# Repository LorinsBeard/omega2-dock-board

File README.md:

# Omega2 Dock board

Inspired by [Omega dock\new](https://github.com/5N44P/omega-dock-new) board.

## Overview

This is yet another dock for Onion Omega2/Omega2+ single board computers. 
Main board features:

* Ethernet socket
* USB type A Host
* Micro USB power and UART
* Expansion pins
* User Button and LED

## BOM

BOM is also available in CSV format.

| Reference | Quantity | Description | MPN | Manufacturer | Datasheet |
|-----------|---------:|-------------|-----|--------------|-----------|
| C10 C2  | 2 | CAP CER 10UF 6.3V X5R 0603 | CL10A106MQ8NNNC | Samsung Electro-Mechanics | [link](http://www.samsungsem.com/kr/support/product-search/mlcc/__icsFiles/afieldfile/2018/06/20/CL10A106MQ8NNNC.pdf) |
| C4 C5  | 2 | CAP CER 22pF 50V NPO 0603 | CL10C220JB8NNN | Samsung Electro-Mechanics | [link](www.samsungsem.com/global/front/downloadcms.do?path=%2F%2Fglobal%2F%2Fsupport%2F%2Fproduct-search%2F%2Fmlcc%2F%2F__icsFiles%2F%2Fafieldfile%2F%2F2016%2F%2F08%2F%2F18&fileName=S_CL10C220JB8NNNL.pdf) |
| C6 C8 C7 C1 C3  | 5 | CAP CER 0.1UF 50V X7R 0603 | CL10B104KB8NNNC | Samsung Electro-Mechanics | [link](http://www.samsungsem.com/kr/support/product-search/mlcc/__icsFiles/afieldfile/2018/07/24/CL10B104KB8NNNC.pdf) |
| C9  | 1 | CAP CER 1UF 16V X7R 0603 | CL10B105KO8NNNC | Samsung Electro-Mechanics | [link](http://www.samsungsem.com/kr/support/product-search/mlcc/__icsFiles/afieldfile/2019/06/18/CL10B105KO8NNNC-19.pdf) |
| D2 D1  | 2 | TVS DIODE 5.25V 17V SOT23-6 | USBLC6-2SC6 | STMicroelectronics | [link](http://www.st.com/content/ccc/resource/technical/document/datasheet/06/1d/48/9c/6c/20/4a/b2/CD00050750.pdf/files/CD00050750.pdf/jcr:content/translations/en.CD00050750.pdf) |
| D3 D4  | 2 | LED Yellow Green 0603 30mA | FYLS-0603GD | FORYARD OPTOELECTRONICS | [link](http://www.foryard-led.ru/pdf/fyls-0603gd.pdf) |
| F1  | 1 | PTC RESET FUSE 6V 1.1A 1206 | MF-NSMF110-2 | Bourns | [link](https://www.bourns.com/docs/Product-Datasheets/mfnsmf.pdf) |
| J1  | 1 | CONN RCPT USB2.0 MICRO B SMD R/A | 10118194-0001LF | Amphenol ICC (FCI) | [link](http://www.amphenol-icc.com/media/wysiwyg/files/drawing/10118194.pdf) |
| J2  | 1 | CONN RCPT USB2.0 TYPEA 4POS R/A | KLS1-181A-W | KLS | [link](http://www.klsele.com/admin/product_upload/20190917081512KLS1-1811%20A%20Female%20Dip%2090%20USB%20Connector%202.jpg.pdf) |
| J3  | 1 | CONN F HEADER 26POS 2.54mm | ZL262-26DG | CONNFLY | [link](http://www.kosmodrom.com.ua/pdf/zl262-dg.pdf) |
| J4  | 1 | CONN M HEADER 6 POS 2.54mm | ZL201-06G | CONNFLY | [link](http://www.kosmodrom.com.ua/pdf/zl201.pdf) |
| J5  | 1 | RJ45 connector with transformer | KLS12-TL002R-1*1-G/Y-1-03 | KLS | [link](http://www.klsele.com/admin/product_upload/20170620132005KLS12-TL002-1X1.pdf) |
| R1 R3  | 2 | SMD RES 0603 10 kOhm 100mW 50V | RC0603FR-10KR | Hitano | [link](https://www.rcscomponents.kiev.ua/datasheets/komechip-eesistor-datasheet.pdf) |
| R11 R7 R6 R10  | 4 | SMD RES 0603 49.9 Ohm 100mW 50V | RC0603FR-49R9 | Hitano | [link](https://www.rcscomponents.kiev.ua/datasheets/rc_series_hitano-datasheet.pdf) |
| R12 R4 R5 R8 R9 R2 R13  | 7 | SMD RES 0603 470 Ohm 100mW 50V | RC0603JR-470R | Hitano | [link](https://www.rcscomponents.kiev.ua/datasheets/rc_series_hitano-datasheet.pdf) |
| SW2 SW1  | 2 | SWITCH TACTILE SPST-NO 0.05A 12V | TACTM-24N-F | NINIGI | [link](https://en.ninigi.com/product/tactm-24n-f/pdf) |
| U1  | 1 | USB UART CONVERTER 16SOIC | CH340G | WCH | [link](www.datasheet5.com/pdf-local-2195953) |
| U2  | 1 | SBC  | Omega2 | Onion | [link](https://docs.onion.io/omega2-docs/omega2p.html) |
| U3  | 1 | IC REG LINEAR 3.3V 800MA SOT223  | LD1117S33TR | STMicroelectronics | [link](https://www.st.com/content/ccc/resource/technical/document/datasheet/99/3b/7d/91/91/51/4b/be/CD00000544.pdf/files/CD00000544.pdf/jcr:content/translations/en.CD00000544.pdf) |
| Y1  | 1 | Quartz Crystal SMD 12.0 MHz | 12.88662 | GEYER | [link](https://www.geyer-electronic.com/fileadmin/user_upload/frequenz/quartz/KX-7/GEYER-KX-7.pdf) |

Note:

I have bought a KLS Ethernet connector for **J5** but used a footprint for [Amphenol ICC RJMG1BD3B8K1ANR](https://www.digikey.com/product-detail/en/amphenol-icc-commercial-products/RJMG1BD3B8K1ANR/RJMG1BD3B8K1ANR-ND/5359794) connector. There is just one difference - **reversed pinout** for Yellow LED. 

Also, I have bought a KLS USB A connector for **J2** and used an [Amphenol ICC UE27AC54100](https://www.digikey.com/product-detail/en/amphenol-icc-commercial-products/UE27AC54100/UE27AC54100-ND) footprint, but they are similar, though.

## Schematic & PCB

Designed using **KiCAD**. Also, I have take some parts from [Digi-Key Kicad library](https://www.digikey.com/en/resources/design-tools/kicad). 

The library with footprints is available at the project directory [omega-dock](./omega-dock).

Board has user **Button** at **GPIO11** and **LED** at **GPIO17**. To able these ones just solder bridges **SB1** and **SB4**.

Also, to able Ethernet LEDs solder bridges **SB2** and **SB3**.

## Known bugs

I have realized that there is no fuse for a USB power socket and it may cause damage to the USB port on your PC. So, it recommends using USB 3.0 and higher.

## Other photos

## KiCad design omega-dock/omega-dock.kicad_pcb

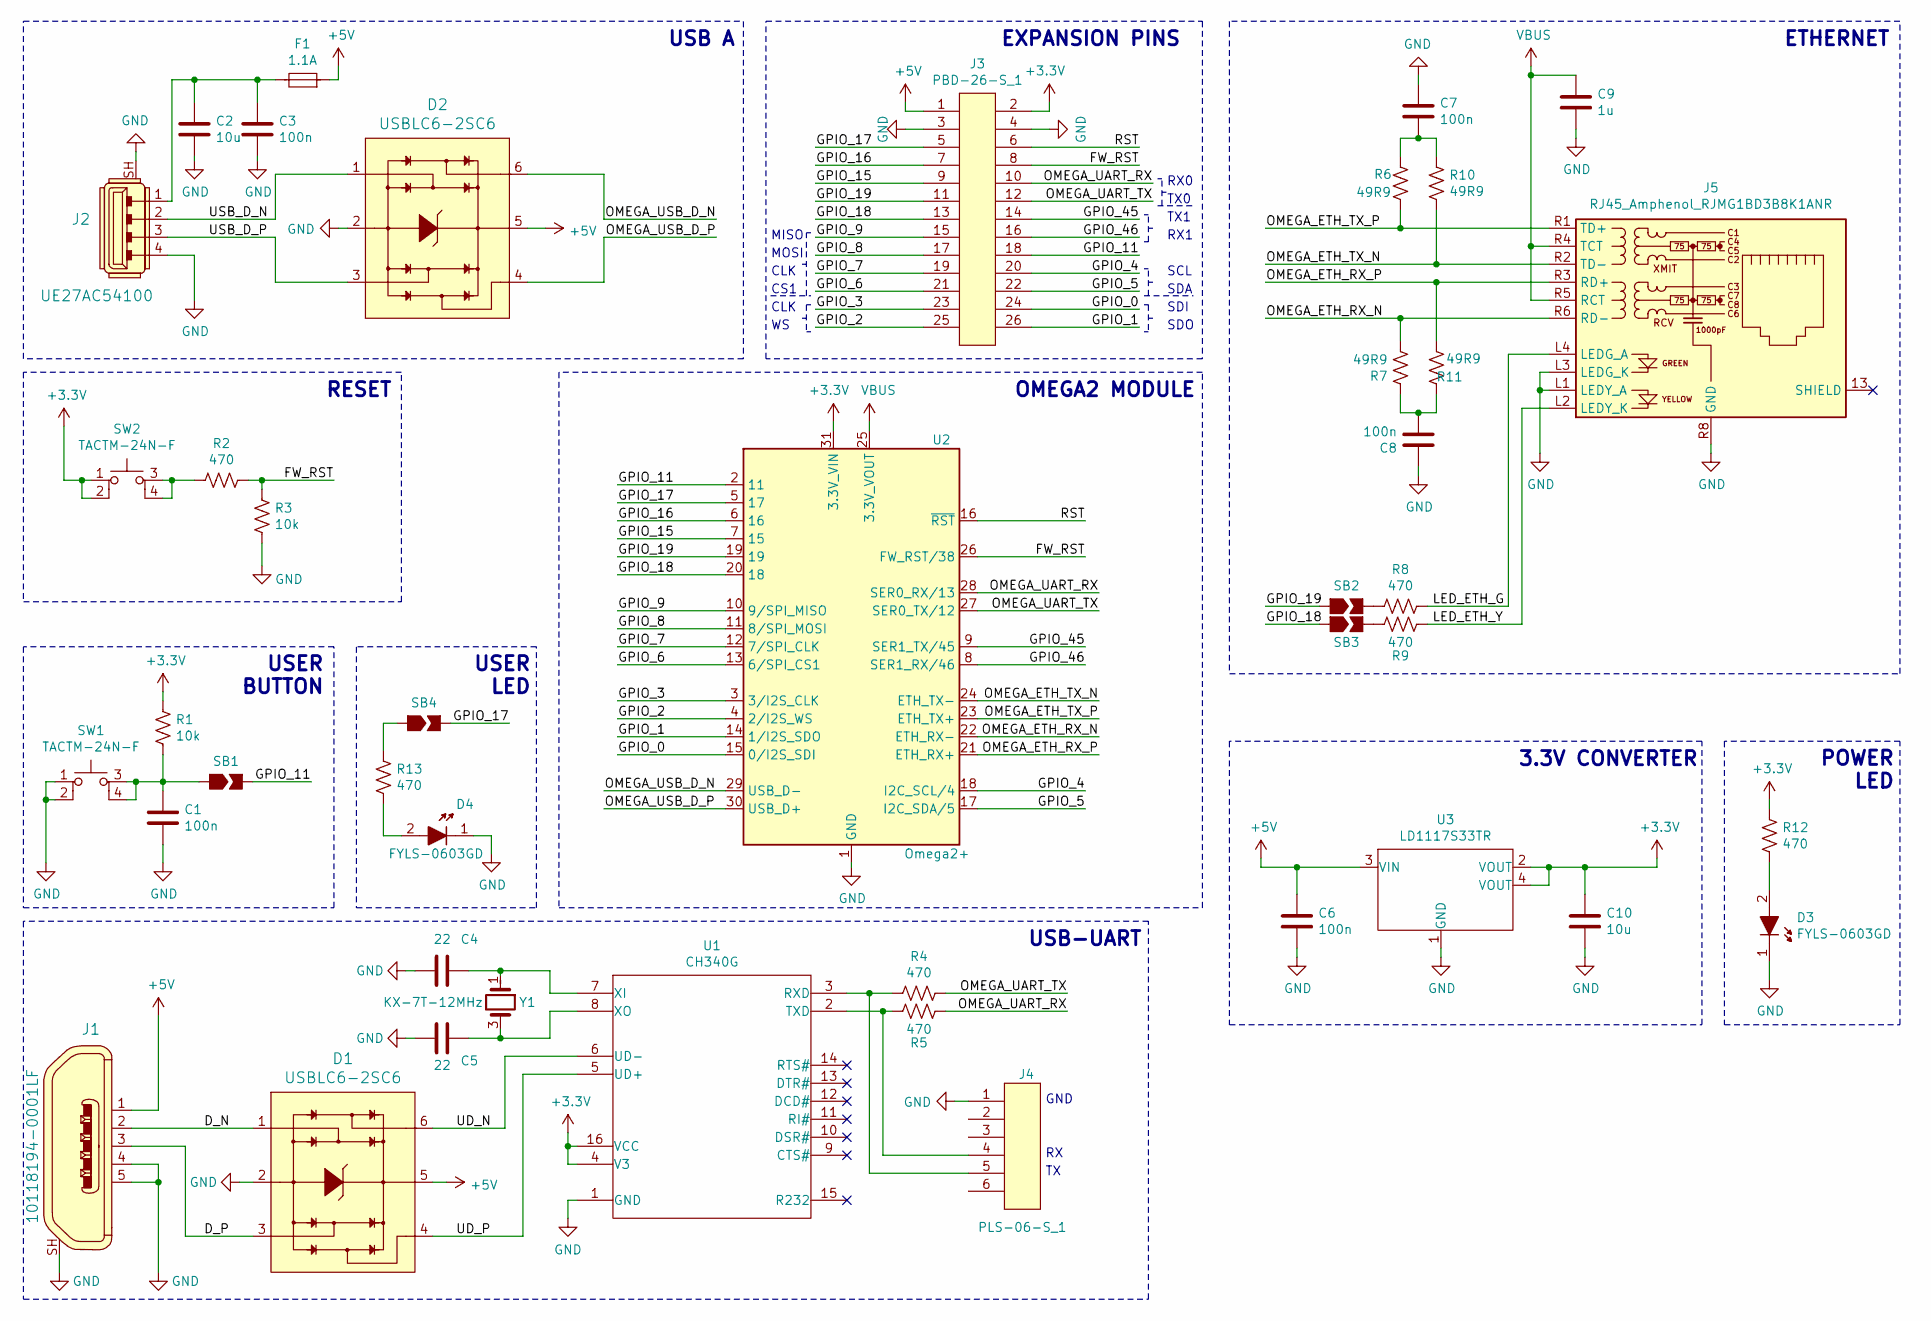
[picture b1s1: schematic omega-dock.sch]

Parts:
C1, C3, C6, C7, C8: 100n_0603_1; C_0603; MPN CL10B104KB8NNNC
C2, C10: 10u_0603_1; C_0603; MPN CL10A106MQ8NNNC
C4, C5: 22p_0603_1; C_0603; MPN CL10C220JB8NNN
C9: 1u_0603_1; C_0603; MPN CL10B105KO8NNNC
D1, D2: USBLC6-2SC6; SOT23-6L; MPN USBLC6-2SC6; Digi-Key_PN 497-5235-1-ND
D3, D4: FYLS-0603GD; LED_0603_1; MPN FYLS-0603GD
F1: MF-NSMF110; Fuse_BOURNS_MF-NSMF; MPN MF-NSMF110-2
J1: 10118194-0001LF; USB_Micro_B_Female_10118194-0001LF; MPN 10118194-0001LF; Digi-Key_PN 609-4618-1-ND
J2: UE27AC54100; USB_A_Female_UE27AC54100; MPN UE27AC54100; Digi-Key_PN UE27AC54100-ND
J3: PBD-26-S_1; MPN ZL262-26DG
J4: PLS-06-S_1; MPN ZL201-06G
J5: RJ45_Amphenol_RJMG1BD3B8K1ANR
R1, R3: 10K_0603_1; R_0603; MPN RC0603FR-10KR
R2, R4, R5, R8, R9, R12, R13: 470R_0603_1; R_0603; MPN RC0603JR-470R
R6, R7, R10, R11: 49R9_0603_1; R_0603; MPN RC0603FR-49R9
SB1, SB2, SB3, SB4: SB_0603_1; SB_0603_TRIANGLE
SW1, SW2: TACTM-24N-F; PUSHB_TL3300DF260Q; MPN TACTM-24N-F
U1: CH340G; SOIC-16; MPN CH340G
U2: Omega2+; Onion_Omega2+
U3: LD1117S33TR; SOT-223; MPN LD1117S33TR
Y1: KX-7T-12MHz; KX-7T; MPN 12.88662

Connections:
+3V3: C10.1, J3.2, R1.1, R12.1, SW2.1, SW2.2, U1.4 (V3), U1.16 (VCC), U2.31 (3.3V_VIN), U3.2 (VOUT), U3.4 (VOUT)
+5V: C6.1, D1.5, D2.5, F1.1, J1.1, J3.1, U3.3 (VIN)
/D_N: D1.1, J1.2
/D_P: D1.3, J1.3
/FW_RST: J3.8, R2.1, R3.1, U2.26 (FW_RST/38)
/GPIO_0: J3.24, U2.15 (0/I2S_SDI)
/GPIO_1: J3.26, U2.14 (1/I2S_SDO)
/GPIO_2: J3.25, U2.4 (2/I2S_WS)
/GPIO_3: J3.23, U2.3 (3/I2S_CLK)
/GPIO_4: J3.20, U2.18 (I2C_SCL/4)
/GPIO_5: J3.22, U2.17 (I2C_SDA/5)
/GPIO_6: J3.21, U2.13 (6/SPI_CS1)
/GPIO_7: J3.19, U2.12 (7/SPI_CLK)
/GPIO_8: J3.17, U2.11 (8/SPI_MOSI)
/GPIO_9: J3.15, U2.10 (9/SPI_MISO)
/GPIO_11: J3.18, SB1.2, U2.2 (11)
/GPIO_15: J3.9, U2.7 (15)
/GPIO_16: J3.7, U2.6 (16)
/GPIO_17: J3.5, SB4.2, U2.5 (17)
/GPIO_18: J3.13, SB3.1, U2.20 (18)
/GPIO_19: J3.11, SB2.1, U2.19
/GPIO_45: J3.14, U2.9 (SER1_TX/45)
/GPIO_46: J3.16, U2.8 (SER1_RX/46)
/LED_ETH_G: J5.L4 (LEDG_A), R8.1
/LED_ETH_Y: J5.L2 (LEDY_K), R9.2
/OMEGA_ETH_RX_N: J5.R6 (RD-), R7.2, U2.22 (ETH_RX-)
/OMEGA_ETH_RX_P: J5.R3 (RD+), R11.1, U2.21 (ETH_RX+)
/OMEGA_ETH_TX_N: J5.R2 (TD-), R10.2, U2.24 (ETH_TX-)
/OMEGA_ETH_TX_P: J5.R1 (TD+), R6.1, U2.23 (ETH_TX+)
/OMEGA_UART_RX: J3.10, R5.2, U2.28 (SER0_RX/13)
/OMEGA_UART_TX: J3.12, R4.1, U2.27 (SER0_TX/12)
/OMEGA_USB_D_N: D2.6, U2.29 (USB_D-)
/OMEGA_USB_D_P: D2.4, U2.30 (USB_D+)
/RST: J3.6, U2.16 (~RST)
/UD_N: D1.6, U1.6 (UD-)
/UD_P: D1.4, U1.5 (UD+)
/USB_D_N: D2.1, J2.2
/USB_D_P: D2.3, J2.3
GND: C1.2, C2.2, C3.2, C4.2, C5.2, C6.2, C7.1, C8.1, C9.2, C10.2, D1.2, D2.2, D3.1, D4.1, J1.4, J1.5, J1.SH, J2.4, J2.SH, J3.3, J3.4, J4.1, J5.L1 (LEDY_A), J5.L3 (LEDG_K), J5.R8 (GND), R3.2, SW1.1, SW1.2, U1.1 (GND), U2.1 (GND), U2.32 (GND), U3.1 (GND)
unnamed: C1.1, R1.2, SB1.1, SW1.3, SW1.4
unnamed: C2.1, C3.1, F1.2, J2.1
unnamed: C4.1, U1.7 (XI), Y1.1
unnamed: C5.1, U1.8 (XO), Y1.3
unnamed: C7.2, R6.2, R10.1
unnamed: C8.2, R7.1, R11.2
unnamed: D3.2, R12.2
unnamed: D4.2, R13.2
unnamed: J4.4, R5.1, U1.2 (TXD)
unnamed: J4.5, R4.2, U1.3 (RXD)
unnamed: R2.2, SW2.3, SW2.4
unnamed: R8.2, SB2.2
unnamed: R9.1, SB3.2
unnamed: R13.1, SB4.1
VBUS: C9.1, J5.R4 (TCT), J5.R5 (RCT), U2.25 (3.3V_VOUT)

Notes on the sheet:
RESET
USER BUTTON
OMEGA2 MODULE
USB A
EXPANSION PINS
ETHERNET
USB-UART
3.3V CONVERTER
POWER LED
GND
CLK
MOSI
MISO
CS1
SDO
SDI
SDA
SCL
TX0
RX0
RX1
TX1
USER LED

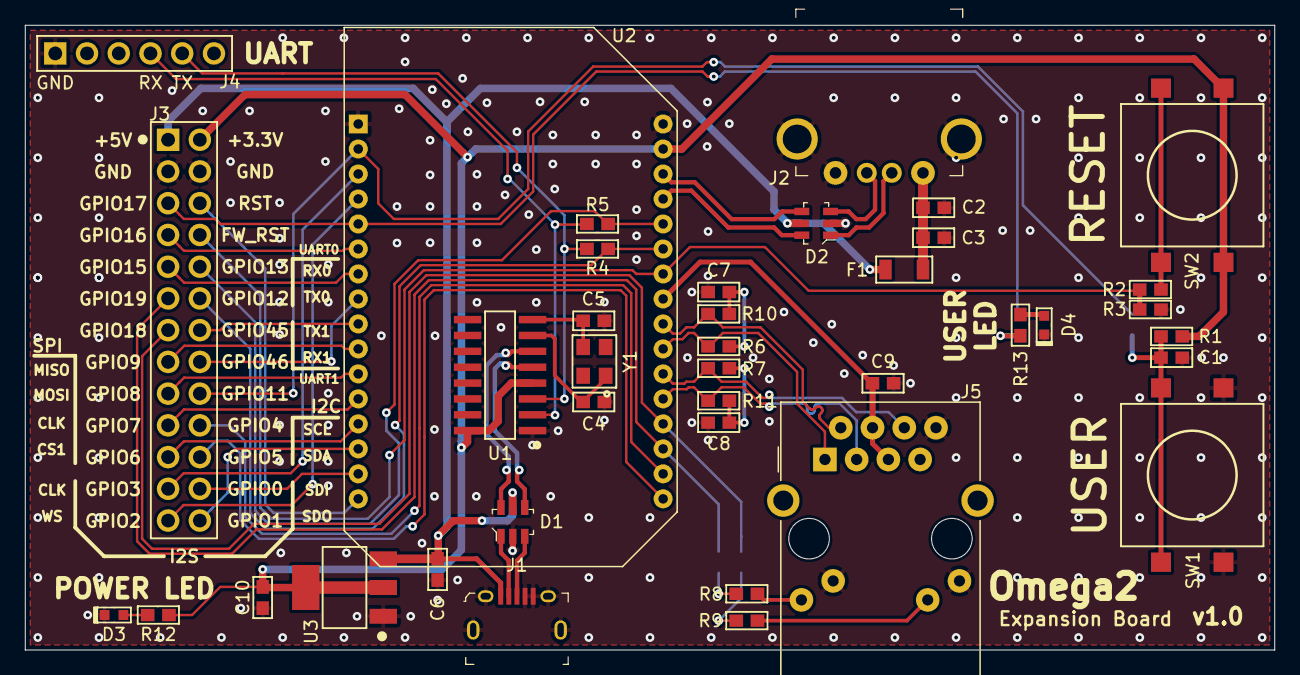
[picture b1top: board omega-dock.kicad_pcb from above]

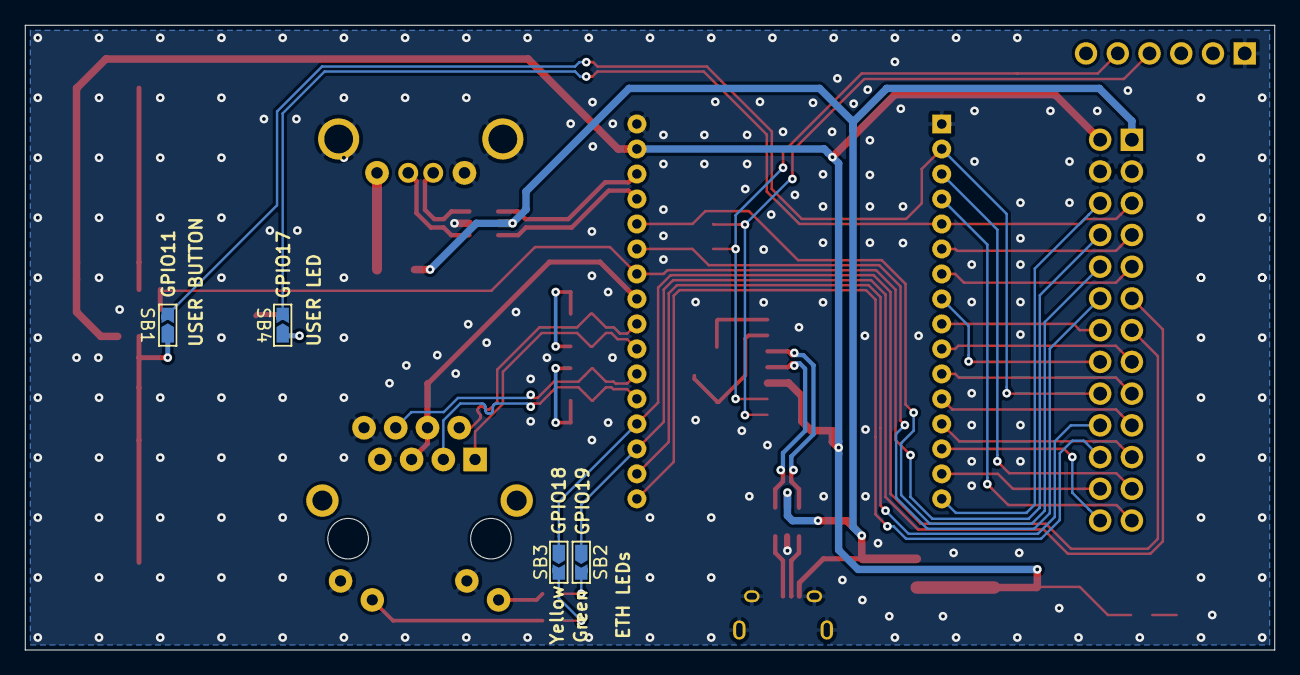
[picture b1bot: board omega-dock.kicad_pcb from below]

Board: 2 copper layers, 100.0 x 50.0 mm, 43 parts (4 on the bottom side), 54 nets.

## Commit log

2020-06-01 Most project files added
